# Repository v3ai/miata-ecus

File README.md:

# miata-ecus

A plug-in [rusEFI](https://rusefi.com) engine computer for the 1989–2005 Mazda Miata (NA and NB). It has two parts:

- **One universal daughterboard.** It does all the engine control: an STM32F407 running rusEFI, plus an on-board
  LSU 4.9 wideband controller (the open-source FOME/rusEFI design).
- **A motherboard for each model year.** Each one fits the stock ECU case, takes the stock harness connector and
  carries the year-specific wiring, the MAP sensor, the wideband sensor plug, the add-on header and USB-C.

The daughterboard plugs into the motherboard on two 1×40 sockets and four M3 standoffs.

<table>
<tr>
<td width="50%"></td>
<td width="50%"></td>
</tr>
<tr>
<td align="center"><sub>Daughterboard lifted off its sockets and standoffs</sub></td>
<td align="center"><sub>The universal daughterboard (rev 0.10)</sub></td>
</tr>
</table>

<sub>Renders from the 3D viewer in <a href="viewer/"><code>viewer/</code></a>, with black solder mask (<code>MASK=black</code> in <code>viewer/pcb3d.py</code>). The harness header, the wideband connector, the card socket, the MAP sensor and the heater fuse F1 are simplified stand-in models.</sub>

**Fitting one to a car:** [INSTALL.md](INSTALL.md) has labelled pictures of every connector, the header pin maps, the
MAP hose and wideband for each year, and the first start.

## Features and limitations

No board has been built yet. "Can" below means the hardware is designed for it and the firmware is set up for it; where
the firmware part has run in [emulation](firmware/sim/), that is as far as the proof goes.

### What it can do

**On every year**
- **Plugs into the stock harness** and fits the stock ECU's case (1990–95; the 1996–2005 fit is unchecked).
- **Fuel from manifold pressure** (speed-density), with the MAP sensor on the board. The stock airflow meter is not
  used and can come out of the intake.
- **MAP sensor good for boost:** 15–700 kPa absolute, so a turbo or supercharger needs no sensor change.
- **Wideband oxygen sensor controller on the board** for a Bosch LSU 4.9. No separate gauge or controller box. The
  board's connector takes AEM's ready-made X-Series sensor harness (30-3427).
- **Closed-loop fuel from the wideband**, switched on from the first start: ±10 % at idle and cruise, +10 / −5 %
  under load.
- **A base tune for each year**, loaded by the year button in TunerStudio ([what is in it](firmware/README.md#base-tune)).
- **Four injector outputs** for high-impedance injectors. Sequential on 1994–2005; in pairs on 1989–93, as the
  stock harness is wired (a jumper pair on that board is for a sequential conversion).
- **Four ignition outputs** (5 V logic): two on the harness for the stock coils, two more on the AUX header for one
  coil per cylinder.
- **Closed-loop idle** (on cars with a throttle position sensor), radiator fan, second fan, A/C clutch, fuel pump,
  check-engine light and tachometer, on the stock wires.
- **One USB-C port** for tuning (TunerStudio) and firmware updates, including the wideband's firmware.
- **Logging to a microSD card** in a socket on the daughterboard (rusEFI's own logger).
- **Protected outputs.** Every driver limits its current and shuts down when it overheats. In simulation every
  harness pin was shorted to ground, 14.4 V and 24 V; what still fails is listed in
  [VERIFICATION.md](VERIFICATION.md#rev-08-driver-temperature-and-protected-outputs).

**By year**

| | 1989–93 | 1994–95 | 1996–97 | 1999–2000 | 2001–05 |
|---|---|---|---|---|---|
| Injection | pairs | sequential | sequential | sequential | sequential |
| Variable valve timing | – | – | – | – | closed loop, rusEFI's target table |
| Knock sensor | add your own | add your own | add your own | stock sensor | stock sensor |
| Alternator voltage | alternator's own | alternator's own | alternator's own | ECU, ships off | ECU, ships off |
| Main relay held by the ECU | – | – | – | – | 2003–05 |
| Stock oxygen-sensor heater | – | – | driven | driven | not driven |
| Throttle position | switch only on manual cars | sensor | sensor | sensor | sensor |

**For a turbo and other add-ons** (the 20-pin add-on header, [pin map](INSTALL.md#header-pin-maps))
- Boost-control valve output, already assigned in the firmware, with a fused 12 V for the valve.
- **Flex-fuel sensor input** (GM / Continental type).
- **Nitrous arming input** for rusEFI's nitrous control.
- **CAN bus** for a dash or gauges: the bus the on-board wideband reports on.
- Knock sensor input for the cars that have none.
- Coil 3 and coil 4 outputs.
- A spare 0–5 V analog input, two inputs for magnetic (VR) crank and cam sensors, 5 V and a fused 12 V.
- rusEFI's own functions are all in the firmware (launch control, boost by table or closed loop, knock retard,
  general-purpose PWM tables, Lua scripts). None of them is set up or tested on this board.

### What it can't do

- **It is untested.** No board has been assembled, powered or run in a car.
- **The base tune is a starting point.** The tables came from other people's cars. Nobody has tuned them under
  boost, and the 1989–97 fuel table stops at 128 kPa.
- **No drive-by-wire throttle.** Every supported car has a cable throttle; this only matters for an engine swap.
- **High-impedance injectors only**, and the ignition outputs need coils with built-in igniters or the stock
  igniter. They can't drive a bare coil.
- **One wideband**, four cylinders.
- **The stock case has to be cut** for the wideband plug, USB-C, the MAP hose and the add-on ribbon cable. The
  1996–2005 boards still have the 1990–95 outline and mounting holes.
- **The add-on header is a ribbon-cable header inside the case**, not a sealed plug, and its 12 V pin is fused at
  1.1 A.
- **Sustained high rpm in a hot cabin is the thermal limit**, most of all on 1989–93 cars: see
  [Things to know before ordering](#things-to-know-before-ordering).
- **1990–93:** the fuel pump is switched by the airflow meter, so removing the meter needs one added wire
  ([INSTALL.md](INSTALL.md#199093)). Manual cars have no throttle position sensor until one is
  [fitted](#throttle-position-sensor-198993-manual-cars).
- **1999–2005:** alternator control ships switched off until the wire has been checked on a car.
- **Not street legal as an emissions device.** No OBD-II diagnostics or readiness monitors, no immobiliser, and it
  doesn't run the EGR valve, the 1999–2005 purge valve, the 2001–05 intake shutter valves (VTCS) or the rear oxygen
  sensor. The 1999–2000 VICS solenoid is wired but not set up.
- **Automatic cars are untested**, and the transmission unit's signals are mostly left unconnected.
- **2004–05 Mazdaspeed is not supported.**

> **Status:** every board is fully routed and passes KiCad DRC (no clearance errors, no unconnected items), and each
> schematic's netlist has been checked pad-by-pad against its board. **None of them has been built or tested yet**, and
> no person has reviewed the schematics. Read each board's README, especially its *Still to verify* or *Before ordering* list.
>
> **Verification (desk + simulation, 2026-10-30):** [VERIFICATION.md](VERIFICATION.md). Pinouts and firmware check out
> for all five years (after fixing a firmware bug that would have cut fuel and spark on 1996-2002 cars). The hardware
> changes it called for are in daughterboard rev 0.5 and motherboards rev 0.6 (1989-95) / 0.4 (1996-2005):
> - 5 V drive for the low-side drivers, held off until the firmware runs;
> - freewheel diodes on the idle and VVT valves;
> - BOOT1 pull-down;
> - no 2003-05 key-off back-feed;
> - a fused, clamped logic supply and a fused AUX +12 V pin;
> - clamped crank/cam inputs;
> - two drivers per injector wire on 1989-93.
>
> Every fix was re-simulated. Two wires still need checking on a car.
>
> **Full-firmware emulation (2026-11-02):** the unmodified rusEFI firmware runs on an emulated STM32F407 through every
> model year with 0 failures (two firmware bugs found and fixed). It flashes a blank emulated wideband STM32F103, which
> then reports lambda over CAN (`firmware/sim/`). The expanded circuit and fault checks found 13 new hardware items
> (N1-N13). Daughterboard rev 0.7 and the motherboards' 3 A heater fuse fixed most of them; see
> [Rev 0.7](VERIFICATION.md#rev-07-fixes-for-the-2026-11-02-findings).
>
> **Rev 0.8 (2026-11-03):** a larger daughterboard (125 × 76 mm) with DPAK injector drivers on drain copper and thermal
> vias (estimated 110 °C at 90 % duty and 85 °C ambient, where rev 0.7 reached thermal shutdown), protected relay, lamp,
> tach and ignition outputs, a separate protected 5 V for the harness sensors, LSU drive clamps, a +3V3 shunt clamp and
> fault-tolerant CAN transceivers. Every harness cavity shorted to ground, 14.4 V and 24 V: 4 failures left (rev 0.7:
> 215), all the LSU drive resistors taking a battery short so the ICs don't. See
> [Rev 0.8](VERIFICATION.md#rev-08-driver-temperature-and-protected-outputs).
>
> **Rev 0.9:** layout only. J1 is back on the daughterboard's top edge with the driver strip below it, and the
> daughterboard sits 16 mm lower, centred on each motherboard. Re-checked: same results as rev 0.8.
>
> **1989–93 motherboard rev 0.11:** the manual cars' throttle position sensor conversion uses the stock throttle switch
> plug, through three 0 Ω links. Pin 1N is no longer wired straight to the sensor 5 V, which the stock switch would have
> shorted at every idle. See [Throttle position sensor (1989–93 manual cars)](#throttle-position-sensor-198993-manual-cars).
>
> **Rev 0.10 (2026-11-13):** the daughterboard is now six layers in the same outline, with a turn-off clamp per
> injector, a microSD socket and flex-fuel and nitrous inputs; the motherboards take AEM's wideband harness and have a
> 20-pin add-on header with CAN, and 1989–93 and 1994–95 share one board set by jumpers. Before the layout every
> figure the design rests on was read again from its maker's document. That found a series resistor the injector
> drivers' inputs should always have had, and showed that the injector inductance behind every temperature estimate
> was a guess. A model of the whole board's copper now gives those temperatures. See
> [Rev 0.10](VERIFICATION.md#rev-010-six-layers-injector-clamps-card-socket-two-more-inputs-2026-11-13).
>
> **2026-11-14:** the motherboards' wideband connector was the wrong series (a guess); it is now the JST header
> that AEM's instructions point to (motherboards rev 0.13 / 0.9, routed again). The full-firmware emulation was run
> again with the rev 0.10 firmware, and the pictures and 3D viewer were redrawn from the current boards.
>
> **The boards ordered in November 2026** are the set before this (daughterboard rev 0.9). Their files are kept in
> [`ordered-boards/2026-11/`](ordered-boards/2026-11/); what the rev 0.10 review means for them is in
> [VERIFICATION.md](VERIFICATION.md#the-ordered-rev-09-boards).

| Board | Folder | Rev | Harness header | Case fit |
|---|---|---|---|---|
| Daughterboard (all years) | [`daughterboard/`](daughterboard/) | 0.10 | 2 × 1×40 to the motherboard | 125 × 76 mm, 6 layers |
| 1989–95 (NA6 and NA8; jumpers set 1989–93 or 1994–95) | [`motherboards/1989-95/`](motherboards/1989-95/) | 0.13 | TE 174917-6, 48 pins | stock NA case outline |
| 1996–97 (NA8, OBD-II) | [`motherboards/1996-97/`](motherboards/1996-97/) | 0.9 | TE 178780-1, 76 positions | **provisional** (NA outline) |
| 1999–2000 (NB1) | [`motherboards/1999-2000/`](motherboards/1999-2000/) | 0.9 | TE 178780-1, as 1996–97 (the car's own is the 64-position 176122-6; its plugs are the same housings) | **provisional** (NA outline) |
| 2001–05 (NB2, VVT) | [`motherboards/2001-05/`](motherboards/2001-05/) | 0.9 | TE 353830-5, 72 positions | **provisional** (NA outline) |

Each board folder contains:
- the KiCad 7 project (schematic and board);
- a schematic PDF;
- JLCPCB gerbers, BOM and placement files in `fab/`, with the DRC report, named for the board and revision (for example
  `miata-ecu-motherboard-1989-95-rev0.13_jlcpcb_gerbers.zip`). The JLC BOM is the SMD parts (and USB-C);
  `…_self_order_bom.csv` is everything you order and solder yourself, and
  [`additional-parts/order_all_boards.csv`](additional-parts/order_all_boards.csv) adds up every motherboard, a daughterboard for each and the in-car parts
  (the same list as a page with quantities and tick boxes: [`additional-parts/shopping_list.html`](additional-parts/shopping_list.html));
- renders;
- a README with the pinout, assembly notes and open questions.

## Firmware and flashing
The rusEFI board definition is in [`firmware/`](firmware/): pin map, year presets, and a flasher for the wideband MCU.
GitHub Actions builds it on every push: the firmware, the rusEFI console bundle and the TunerStudio `.ini`.
See [`firmware/README.md`](firmware/README.md). It compiles, but hasn't run on hardware yet.
- **One USB-C port for everything.** The USB-C on the motherboard's bottom edge goes to the main MCU (STM32F407).
  - **First flash:** ST's DFU mode (hold BOOT, tap RESET).
  - **Later updates:** from the rusEFI console through the OpenBLT bootloader, with no buttons to press.
  - **Tuning:** TunerStudio over the same port. Popular Vehicles picks the model year; the tune is stored in the
    MCU's flash.
- **The wideband MCU (STM32F103) is programmed through the main MCU.** With the engine off, press "Flash on-board
  wideband" in TunerStudio, or type `wbo_uart_flash` in the rusEFI console.
  - The main MCU controls the F103's BOOT0 and reset lines and writes the wideband firmware through the F103's
    built-in ST serial bootloader. The firmware is rusEFI's wideband controller with this board's port
    (`firmware/wideband`), and the main firmware carries it.
  - The SWD Tag-Connect pads on the bottom of the daughterboard (J102) are a fallback.

## Air temperature sensor
The stock sensor's harness wire goes straight to the ECU's air-temperature input: inside the airflow meter on 1989–97,
in the air filter box on 1999–2005. There is no separate connector for it on the board since motherboard rev 0.12 / 0.8.
With the airflow meter or airbox removed, put an open-element sensor on the stock sensor's plug
([INSTALL.md](INSTALL.md#7-air-temperature)) and pick its curve in TunerStudio. The firmware already accounts for the
board's 2.7 kΩ pull-up and divider.

## Throttle position sensor (1989–93 manual cars)
The 1989–93 manual cars have no throttle position sensor: the part on the throttle body is a switch with an idle
contact and a full-throttle contact. The automatics have a real 0–5 V sensor on 2M, as do all 1994–2005 cars. The ECU
calculates fuel from its MAP sensor, so a manual car runs without one, but rusEFI then treats the throttle sensor as
failed: no closed-loop idle, no throttle-based acceleration fuel and no overrun fuel cut.

The switch's plug has three wires: idle contact (1N), ground (2D) and full-throttle contact (2L). A sensor needs
three: 5 V, ground and signal. So, as on rusEFI's Hellen NA6 and MRE boards, a sensor plugs into the stock plug and the
1989–95 motherboard sets those pins with 0 Ω links: **fit R28** (5 V on 1N) and **move R29 to R30** (2L to
the throttle input). The kit, in the board's self-order BOM as "Manual cars":
- **Sensor:** a Kia sensor with the same 3-pin Mazda plug (Kia 0K01118911, or the others the
  [rusEFI wiki](https://wiki.rusefi.com/Legacy-Miata-NA-48-pin-board-for-MRE) lists).
- **Mount:** [Mazda NA6 Miata variable TPS mount](https://www.thingiverse.com/thing:3414132), printed in ASA.
- **Or instead:** [Flyin' Miata's TPS upgrade kit](https://flyinmiata.com/products/tps-upgrade) with its sensor.

Check the plug's wiring and the sensor's pins on your car before fitting R28: see the
[1989–95 README](motherboards/1989-95/README.md). Automatics leave R28 and R30 off.

## Things to know before ordering
- **Measure one injector's inductance first** (LCR meter, injector unplugged). The heat the injector clamps put into
  the board scales with it, and it is not known for Miata injectors: the design is sized for 20 mH, earlier revisions
  assumed 8 mH. At sustained 7200 rpm with 20 mH injectors the board model puts the processor 32–40 °C above the air
  around the board on 1994–2005 cars and 42–54 °C on 1989–93 cars, against a 105 °C junction rating. The 125 °C grade
  of the processor (STM32F407VGT7) fits the same pads and costs about five times as much. Numbers and options:
  [VERIFICATION.md](VERIFICATION.md#board-temperature).
- **The wideband connector has not been tried with a harness.** The motherboards carry a JST PUD header
  (S08B-PUDSS-1) for AEM's X-Series sensor harness 30-3427. AEM's instructions name the harness's terminal, and that
  terminal belongs to this connector series; AEM does not say which cavity is pin 1, so the board follows JST's
  numbering and prints each pin's wire colour beside the connector. Compare a harness with the print before the first
  use ([INSTALL.md](INSTALL.md#header-pin-maps)).
- **Clamp TVS stock.** The daughterboard's injector clamp TVS (Vishay TPSMC16A) is in JLCPCB's library, but its stock
  could not be confirmed; the [daughterboard README](daughterboard/README.md#before-ordering) names the alternate.
- **1996–2005 case geometry is a placeholder.** These motherboards use the NA board outline and mounting holes until a
  stock 96–97 / NB case is measured. The 76-pin 96–97 header is 130 mm wide and must clear the real case.
- **2001–05 Mazdaspeed:** pin 4R is the second intake-air-temperature sensor on the turbo cars, not the VVT valve.
  Don't fit the 01–05 board to a Mazdaspeed unmodified.
- **Wideband layout is new.** The wideband *circuit* is FOME's proven design. Since daughterboard rev 0.3 its *layout*
  is this board's own, so bring it up and check it against a known sensor before relying on it.
- **MAP sensor:** an MPX5700AP (absolute, single barb), fitted flat with its marking up. The barb's position on the
  footprint was taken from a photo; check it against a real part.

## Repository layout
| Path | What |
|---|---|
| `daughterboard/`, `motherboards/<years>/` | The released boards (see above) |
| `scripts/` | The design source. Every board is generated from Python: parts, netlist, placement, a grid router, schematic generation, release packaging |
| `mb/ecu_mb.pretty/` | Project footprints (harness headers named by OEM terminal, the flat MPX5700AP, USB-C, M4 case hole) |
| `research/` | Pinout research for 1996–2005 (sources compared per pin); the rev 0.10 design audit (every figure the board relies on, its source, and what could not be checked); ST's pin data files |
| `ordered-boards/2026-11/` | The board set ordered in November 2026 (daughterboard rev 0.9), as ordered |
| `viewer/` | Interactive 3D viewer: the daughterboard alone, or assembled on any year's motherboard. Click a part for its details and shop links |
| `firmware/` | The rusEFI board definition, the wideband flasher, the simulation tests and the verification tools. rusEFI itself is a submodule in `firmware/ext/rusefi` |
| `website/` | A black-and-white Shopify theme for selling the boards, draft product listings and product photos ([website/README.md](website/README.md)) |
| `INSTALL.md` | Fitting the ECU to a car: labelled pictures, header pin maps, the MAP hose and wideband per year, first start |
| `images/` | Renders, and the labelled pictures and pin maps (`scripts/annotate.py` redraws those from the board files) |
| `VERIFICATION.md` | Pinout, datasheet, simulation, flashing and safety review, with the hardware changes it calls for |
| `.github/workflows/firmware.yaml` | CI: checks the pin map against the board design and builds the firmware |

## Rebuilding
You need:
- **KiCad 7.0** with its Python `pcbnew` module, and `kicad-cli`;
- **Python 3** with `shapely` 2, `numpy`, `scipy`, `Pillow`, `openpyxl` and `matplotlib`;
- **`rsvg-convert`**, for the renders.

```sh
# daughterboard: build, route, finish, then the release folder
LAYERS=6 scripts/daughter_make.sh work/daughter
scripts/daughter_release.sh work/daughter/finished.kicad_pcb out/daughterboard

# a motherboard: <year module> <short name> <rev>, e.g. 1999-2000
scripts/mb_make.sh mb_nb1 9900 0.9      # writes mb/release_9900
```

Routing takes 10–40 minutes per motherboard and about an hour for the daughterboard.

`mk_hdr_fp.py` reads the harness-header geometry from the rusEFI hellen-one boards and KiCad library. Point it at them
with `MIATA_REF` and `RUSEFI_LIBS`. The generated footprints are already in `mb/ecu_mb.pretty/`.

The firmware build is described in [`firmware/README.md`](firmware/README.md).

The viewer is a static page. To open it, run `cd viewer && python3 -m http.server`, then browse to `http://localhost:8000`.
`viewer/pcb3d.py` rebuilds its assets from a board; it also needs `trimesh`, `cascadio`, `Pillow` and `gltfpack`.

The labelled pictures and pin maps in [INSTALL.md](INSTALL.md) come from the viewer and the board files:
`scripts/annotate.py --three <unpacked three@0.160.0 package>` redraws them (needs Playwright with Chromium, and `Pillow`).
`scripts/render_photos.py` renders the pictures at the top of this page and the shop's product photos the same way,
from a black-mask build of the viewer's assets.

## Credits and licences
- This project (the board designs, scripts and viewer) is released under the [MIT licence](LICENSE).
- One firmware file is GPL-3.0: `firmware/board/miata_nb_tune.cpp` holds the 1999–2005 base tune tables, copied from
  rusEFI. The firmware you build includes rusEFI, so the built firmware is GPL-3.0 as a whole
  ([firmware/README.md](firmware/README.md#licences)).
- The wideband controller circuit is the FOME / rusEFI open-source wideband module
  ([mck1117/wideband](https://github.com/mck1117/wideband), `board_module` rev C, MIT licence). Its source files and
  licence are in `scripts/wideband_ref/`.
- The circuit topologies follow rusEFI's hellen-one modules, and the harness pinouts were cross-checked against the
  rusEFI hellen Miata boards and the Mazda workshop manuals (see `research/`).

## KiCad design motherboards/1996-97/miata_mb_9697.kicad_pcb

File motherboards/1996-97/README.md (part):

# Miata ECU motherboard 1996-1997 (NA8 OBD2), rev 0.9

The motherboard replaces the stock Mazda ECU board inside the **stock ECU case**. It carries:

- the stock harness header;
- the year-independent I/O: the wideband sensor connector (AEM X-Series harness), USB-C, the MAP sensor and the add-on header (flex fuel, nitrous, CAN, boost);
- the sockets for the universal daughterboard, which does all the engine control (including the wideband controller).

## Changes in this revision
- Rev 0.9: the wideband sensor connector J2 is now a JST PUD side-entry header (S08B-PUDSS-1, two rows of four at 2.0 mm) instead of rev 0.8's Molex Micro-Fit 2x4. AEM's instructions for the X-Series gauge name the harness's replacement terminal, JST SPUD-001T-P0.5, which is the contact of JST's PUD series (plug housing PUDP-08V-S): a Micro-Fit header would not have taken the plug. The wire colour of each pin is printed beside the connector, to check a harness against by eye. The board is routed again; nothing else changed.
- Rev 0.8, for daughterboard rev 0.10 (a rev 0.9 daughterboard fits too, without the new functions). The wideband sensor connector J2 is a Molex Micro-Fit 2x4 for the off-the-shelf AEM X-Series sensor harness (30-3427) instead of the 2x3 for a hand-made lead; that plug family was a guess, and wrong: corrected in rev 0.9. The separate air-temperature connector J3 and its jumper are gone: the stock sensor's harness wire goes straight to the air-temperature input. The add-on header J5 is a 2x10 box header for a ribbon cable and gains the flex-fuel input (4.7k pull-up to 5 V, R35), the nitrous arming input (10k pull-down, R36) and the CAN bus; a boost valve on it has its own freewheel diode (D5), and its +12 V fuse F4 holds 1.1 A instead of 0.5 A. Harness header TE 178780-1 as before.
- Rev 0.7, for daughterboard rev 0.9: the daughterboard sits 16 mm lower, centred on the board (42 mm from the top, as up to rev 0.7), with its J1 on its top edge again: JD1 and the upper standoffs HD1/HD2 are back at their rev 0.7 places, JD2, the lower standoffs HD3/HD4, the AUX header J5 (with F4 beside it) and the parts placed against JD2 (CAN termination R1/R6, pull-up options) are 16 mm lower, and the board is routed again. Not compatible with a rev 0.8 daughterboard.
- Rev 0.6, for daughterboard rev 0.8: the harness's sensor 5 V (3I) and the AUX header pin J5-14 now come from the daughterboard's protected 5 V (V5_EXT, JD1 pin 13, which was a ground pin): a sensor 5 V wire shorted to the battery no longer back-feeds the MAP sensor and the ECU's own 5 V. The MAP sensor keeps its own supply (V5_SENS). The daughterboard outline on the silkscreen is 16 mm taller (125 x 76 mm): its new strip of output drivers overhangs the free area above JD1.
- Rev 0.5: LSU heater fuse F1 is a 3 A hold PTC (LUTE 2920L300/30GR, 30 V, 2920 size) instead of the 2 A 1812 part. A cold LSU 4.9 heater draws 1.6-2.3 A rms at the start of the wideband's warm-up, more than the old fuse holds once warm, so it could trip and the controller time out. No 1812 PTC holds 3 A above 8 V.
- Rev 0.4: freewheel diode D1 on the idle valve to its +12 V feed (the PWM turn-off energy no longer goes into the daughterboard driver); F4 resettable fuse on the AUX +12 V pin J5-15; not-fitted 12 V pull-up options R20-R22 for the VSS / A/C / clutch inputs.
- Rev 0.3: IAT source is now a removable jumper (JP1, 1x3 2.54 mm header + shunt) instead of the R4 / R5 0R links: shunt on EXT (default) reads the IAT connector J3, on STOCK the stock harness sensor; labelled on the silkscreen.
- Rev 0.2: MAP sensor is now the MPX5700AP (absolute, case 867B, one barb; LCSC C90152) instead of the MPX5700DP: new footprint with the real lozenge body and offset barb, holes on the NXP 23.11 mm spacing with 3.3 mm M3 clearance drills.
- Rev 0.1: first release (design complete, case geometry provisional).

## Files
| Path | What |
|---|---|
| `miata_mb_9697.kicad_pro / .kicad_sch / .kicad_pcb` | KiCad 7 project. Root schematic plus three sheets: harness, daughterboard, I/O |
| `miata_mb_9697_schematic.pdf` | Schematic PDF |
| `fab/miata-ecu-motherboard-1996-97-rev0.9_jlcpcb_gerbers.zip`, `fab/miata-ecu-motherboard-1996-97-rev0.9_jlcpcb_bom.csv`, `fab/miata-ecu-motherboard-1996-97-rev0.9_jlcpcb_cpl.csv` | JLC fabrication and assembly files (2 layers, 1.6 mm). The JLC BOM is the SMD parts and USB-C only |
| `fab/miata-ecu-motherboard-1996-97-rev0.9_self_order_bom.csv` | Everything you order and fit yourself: harness header, through-hole connectors, MAP sensor, shunt, standoffs and screws, plus the not-fitted options. Its columns load into LCSC's BOM tool |
| `fab/miata-ecu-motherboard-1996-97-rev0.9_parts_list.csv` | Every part, including the hand-fitted and not-fitted ones |
| `fab/drc_report.txt` | KiCad DRC |
| `ecu_mb.pretty/`, `fp-lib-table` | Project footprints (harness header, MAP sensor lying flat, USB-C, M4 case hole) |
| `renders/` | Top and bottom copper |
| `scripts/` | The design source; `mb_make.sh` rebuilds the whole board |

## Case fit
**PROVISIONAL.** No source gives this case's board outline and mounting holes yet (the open-source boards for these years either use their own enclosure or a different Mazda case). Until a stock board or case is measured, this board uses the NA case outline and holes as a stand-in, with the header centred on the top edge. Moving to the real outline is a change of OUTLINE / CASE_HOLES / HDR_1A in the year module plus an automatic reroute. **Do not order this board before the case is measured.**

Board: **154.0 × 161.5 mm**, 1.6 mm. The origin is the top-left corner and y points down, toward the bottom edge.

| Hole | x, y (mm) |
|---|---|
| H3 | 4.0, 84.0 |
| H4 | 150.0, 84.0 |
| H5 | 4.0, 143.0 |
| H6 | 150.0, 143.0 |

All holes are 4.5 mm plated with a 7 mm pad, tied to GND, for M4 screws. Harness header terminal 1A sits at (16.00, 18.13) mm (lower pin row).

## Harness header
TE **178780-1**, 76 positions (alternates 174915-6, 3-178780-6): OEM plug 1 = 1A-1V (22), plug 2 = 2A-2L (12, no harness plug: left open), plug 3 = 3A-3P (16), plug 4 = 4A-4Z (26). Hellen's board names the same cavities 1 / 4 / 2 / 3. Fitted by hand.

| Pin | Net | Use | Stock function / note |
|---|---|---|---|
| 1A | `OUT_FAN` | fan relay | cooling (radiator) fan relay |
| 1B | `OUT_LS7` | spare low side | fan No.2 / A/C condenser fan relay |
| 1E | `OUT_CEL` | check engine lamp | MIL |
| 1G | `OUT_AC` | A/C relay | A/C relay |
| 1K | `IN_SW2` | 12 V switch input 2 | A/C switch / refrigerant pressure switch |
| 1L | `IN_SW3` | 12 V switch input 3 | clutch switch |
| 1M | `IN_SW1` | 12 V switch input 1 | vehicle speed sensor |
| 1O | `GND` | ground | ground |
| 1U | `OUT_FP` | fuel pump relay | fuel pump relay |
| 3B | `IN_AUX3` | spare analog 3 | MAF signal |
| 3C | `IN_AUX2` | spare analog 2 | front HO2S (narrowband) |
| 3D | `IN_AUX1` | spare analog 1 | rear HO2S |
| 3F | `IN_TPS` | TPS | throttle position sensor |
| 3G | `IN_CLT` | coolant temp | coolant temperature sensor |
| 3I | `V5_EXT` | sensor 5 V reference (out; protected, short-to-battery proof) | +5 V sensor reference (TPS, MAF) |
| 3K | `IN_IAT` | air temperature (stock sensor) | intake air temperature sensor (in the airflow meter) |
| 3M | `OUT_VVT` | PWM low side (VVT driver) | front HO2S heater (PWM low side; no VVT on this engine) |
| 3O | `GND` | ground | sensor ground (BLK/BLU) |
| 4A | `GND` | ground | ground |
| 4B | `VBAT_IN` | ECU power (main relay) | ECU +12 V from the main relay (WHT/RED) |
| 4C | `GND` | ground |  |
| 4D | `GND` | ground |  |
| 4F | `IN_HALL1` | hall input 1 (crank) | CAS 4-pulse crank angle (SGT), hall / open collector |
| 4G | `IN_HALL2` | hall input 2 (cam) | CAS 2-pulse cam (SGC), hall / open collector |
| 4L | `OUT_TACH` | tach out | tachometer |
| 4N | `OUT_IGN1` | ignition 1 (5 V logic) | igniter cylinders 1 & 4 |
| 4Q | `OUT_IACV` | idle air valve | idle air control valve (low side) |
| 4R | `OUT_IGN2` | ignition 2 (5 V logic) | igniter cylinders 2 & 3 |
| 4U | `OUT_INJ1` | injector 1 |  |
| 4V | `OUT_INJ2` | injector 2 |  |
| 4W | `OUT_INJ3` | injector 3 |  |
| 4X | `OUT_INJ4` | injector 4 |  |

Not connected: 1C, 1D, 1F, 1H, 1I, 1J, 1N, 1P, 1Q, 1R, 1S, 1T, 1V, 2A, 2B, 2C, 2D, 2E, 2F, 2G, 2H, 2I, 2J, 2K, 2L, 3A, 3E, 3H, 3J, 3L, 3N, 3P, 4E, 4H, 4I, 4J, 4K, 4M, 4O, 4P, 4S, 4T, 4Y, 4Z.

## Bottom edge, left to right
| Ref | What | Notes |
|---|---|---|
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
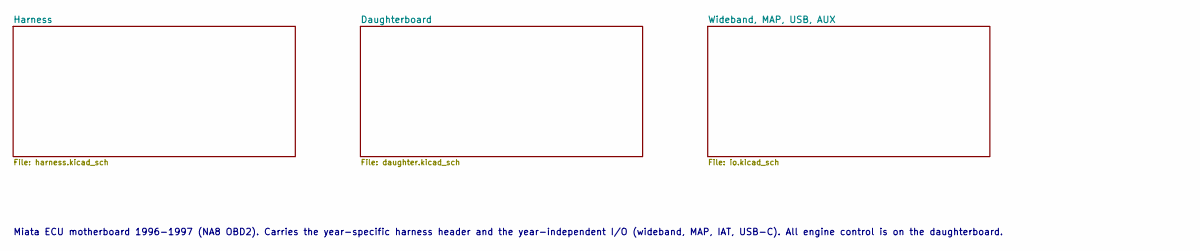
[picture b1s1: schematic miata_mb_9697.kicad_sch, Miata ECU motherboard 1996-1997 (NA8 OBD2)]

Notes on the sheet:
Miata ECU motherboard 1996-1997 (NA8 OBD2). Carries the year-specific harness header and the year-independent I/O (wideband, MAP, IAT, USB-C). All engine control is on the daughterboard.

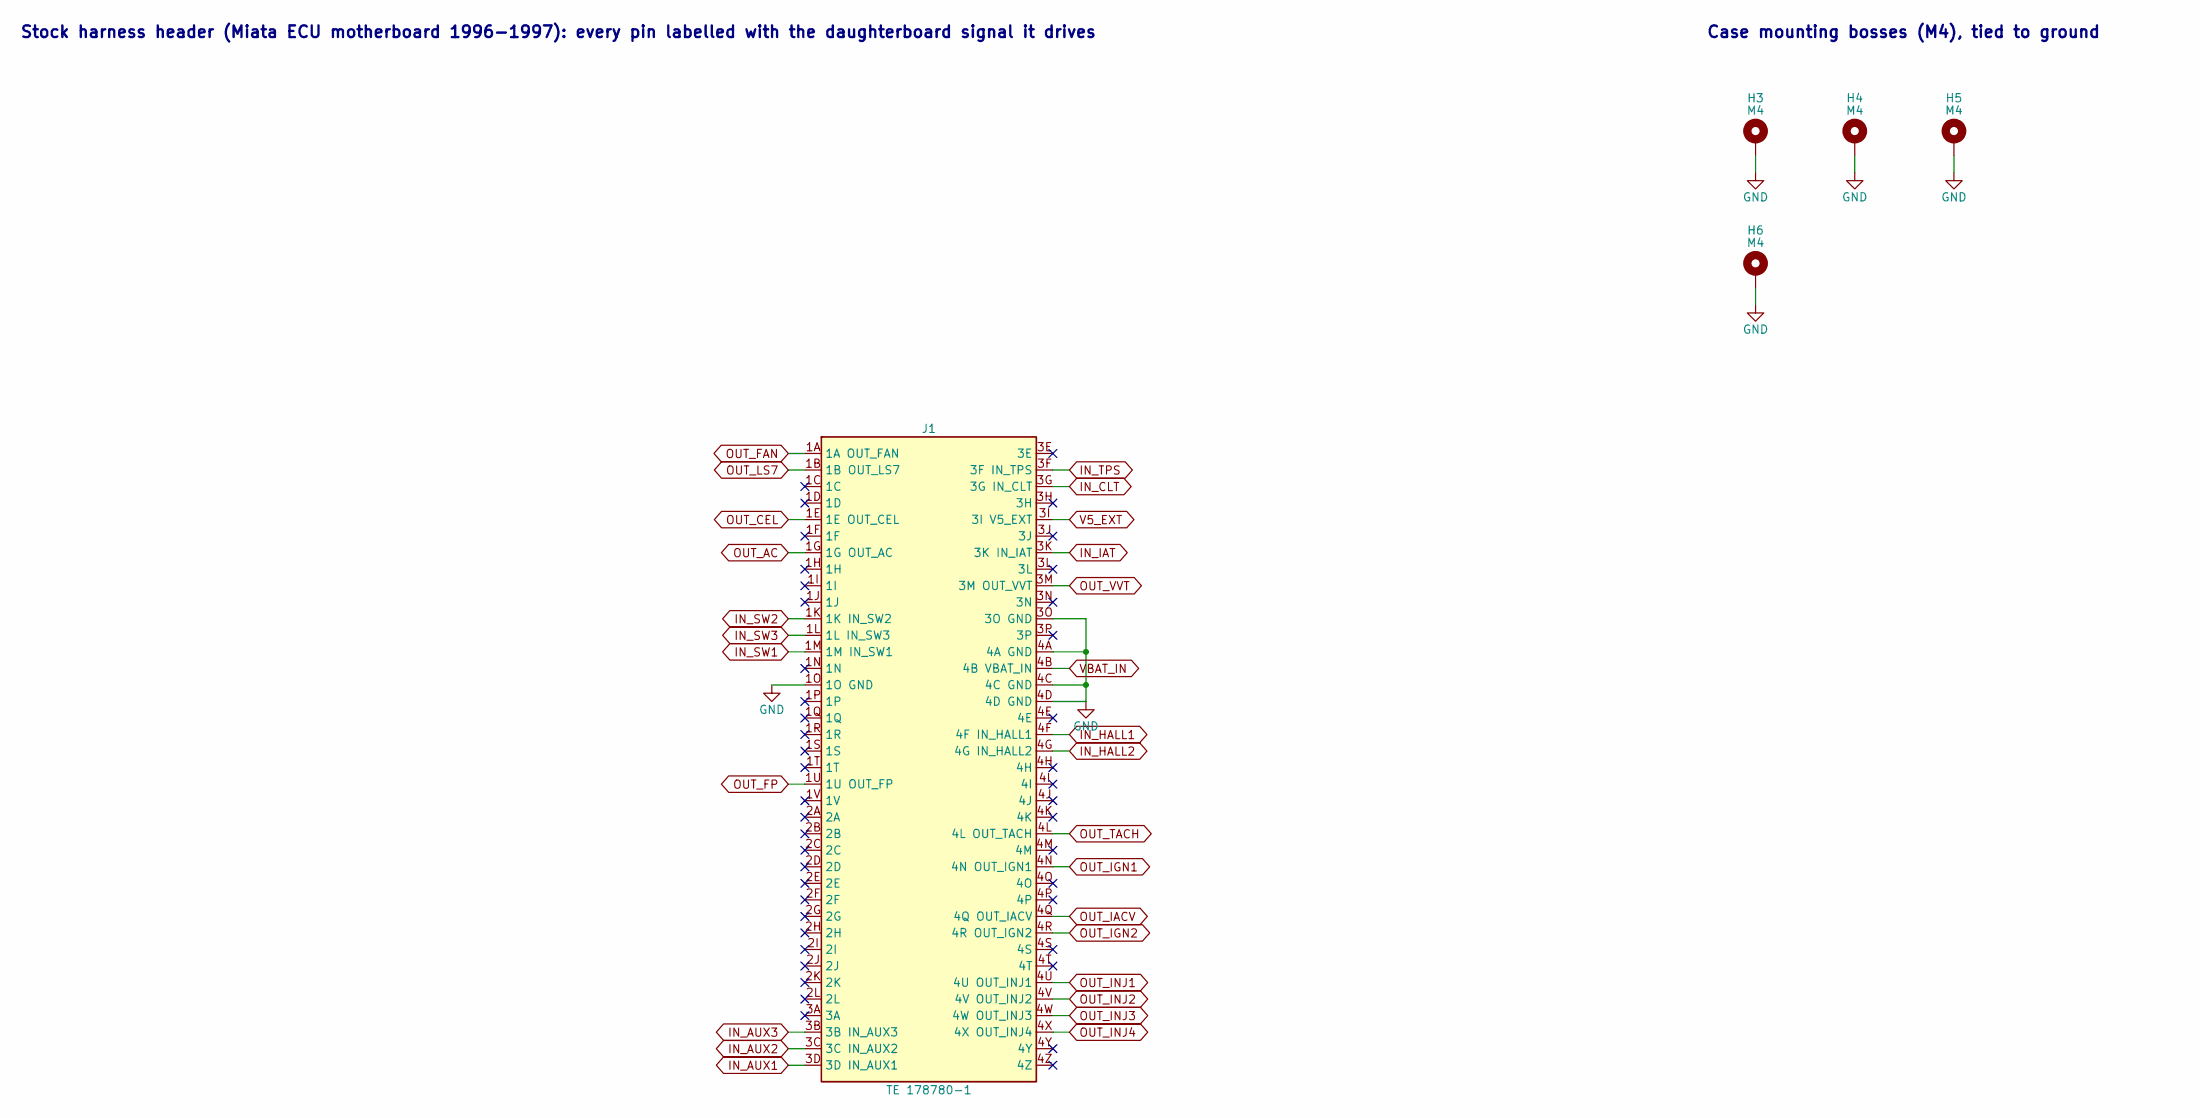
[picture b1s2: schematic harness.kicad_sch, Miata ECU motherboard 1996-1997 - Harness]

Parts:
H3, H4, H5, H6: M4; MountingHole_M4_4.5mm_Pad7
J1: TE 178780-1; TE_178780-1_76P

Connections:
GND: H3.1, H4.1, H5.1, H6.1, J1.1O (1O GND), J1.3O (3O GND), J1.4A (4A GND), J1.4C (4C GND), J1.4D (4D GND); also elsewhere on the board
IN_AUX1: J1.3D (3D IN_AUX1); also elsewhere on the board
IN_AUX2: J1.3C (3C IN_AUX2); also elsewhere on the board
IN_AUX3: J1.3B (3B IN_AUX3); also elsewhere on the board
IN_CLT: J1.3G (3G IN_CLT); also elsewhere on the board
IN_HALL1: J1.4F (4F IN_HALL1); also elsewhere on the board
IN_HALL2: J1.4G (4G IN_HALL2); also elsewhere on the board
IN_IAT: J1.3K (3K IN_IAT); also elsewhere on the board
IN_SW1: J1.1M (1M IN_SW1); also elsewhere on the board
IN_SW2: J1.1K (1K IN_SW2); also elsewhere on the board
IN_SW3: J1.1L (1L IN_SW3); also elsewhere on the board
IN_TPS: J1.3F (3F IN_TPS); also elsewhere on the board
OUT_AC: J1.1G (1G OUT_AC); also elsewhere on the board
OUT_CEL: J1.1E (1E OUT_CEL); also elsewhere on the board
OUT_FAN: J1.1A (1A OUT_FAN); also elsewhere on the board
OUT_FP: J1.1U (1U OUT_FP); also elsewhere on the board
OUT_IACV: J1.4Q (4Q OUT_IACV); also elsewhere on the board
OUT_IGN1: J1.4N (4N OUT_IGN1); also elsewhere on the board
OUT_IGN2: J1.4R (4R OUT_IGN2); also elsewhere on the board
OUT_INJ1: J1.4U (4U OUT_INJ1); also elsewhere on the board
OUT_INJ2: J1.4V (4V OUT_INJ2); also elsewhere on the board
OUT_INJ3: J1.4W (4W OUT_INJ3); also elsewhere on the board
OUT_INJ4: J1.4X (4X OUT_INJ4); also elsewhere on the board
OUT_LS7: J1.1B (1B OUT_LS7); also elsewhere on the board
OUT_TACH: J1.4L (4L OUT_TACH); also elsewhere on the board
OUT_VVT: J1.3M (3M OUT_VVT); also elsewhere on the board
V5_EXT: J1.3I (3I V5_EXT); also elsewhere on the board
VBAT_IN: J1.4B (4B VBAT_IN); also elsewhere on the board

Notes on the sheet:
Stock harness header (Miata ECU motherboard 1996-1997): every pin labelled with the daughterboard signal it drives
Case mounting bosses (M4), tied to ground

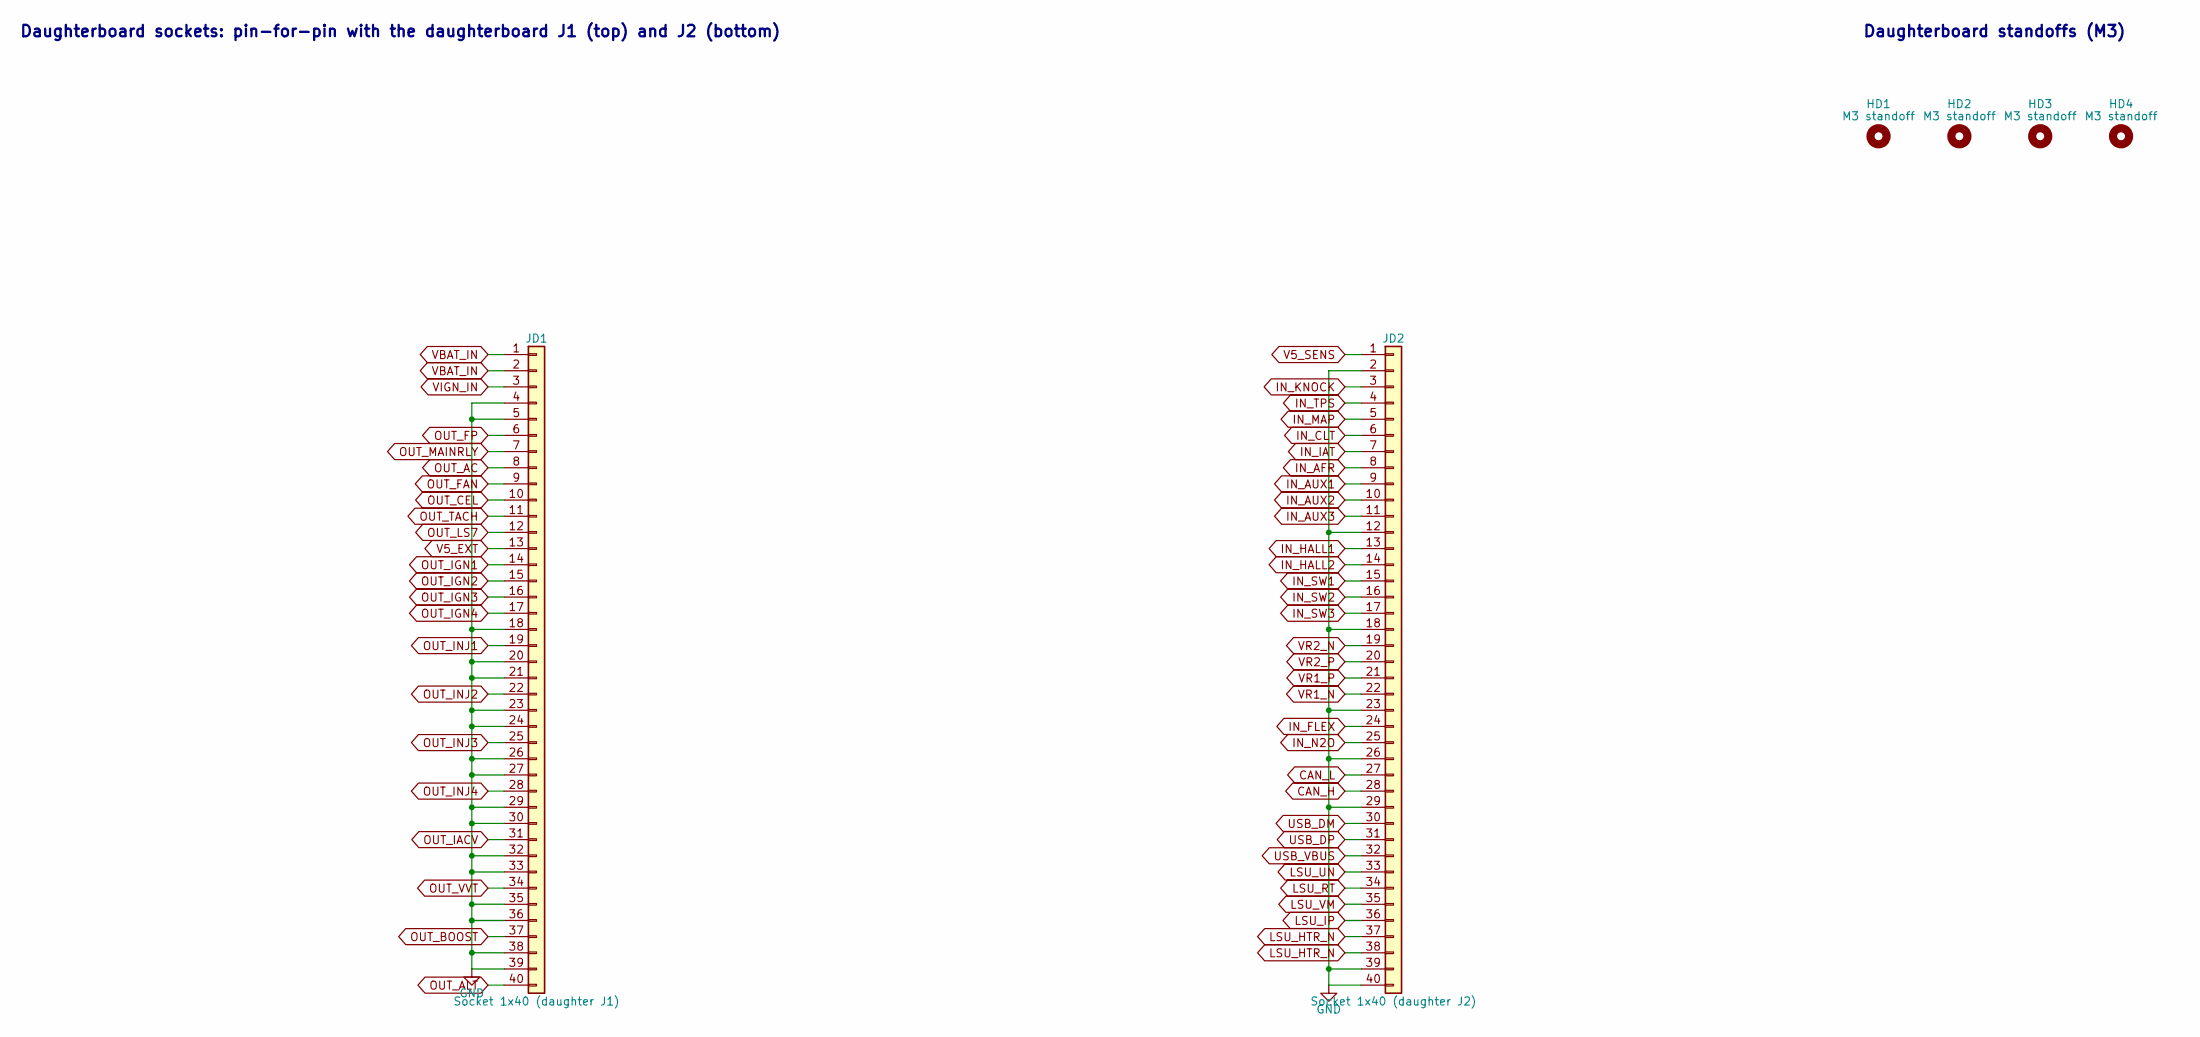
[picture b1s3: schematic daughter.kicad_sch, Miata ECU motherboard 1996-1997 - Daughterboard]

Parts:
HD1, HD2, HD3, HD4: M3 standoff; MountingHole_3.2mm_M3
JD1: Socket 1x40 (daughter J1); PinSocket_1x40_P2.54mm_Vertical; LCSC C124412
JD2: Socket 1x40 (daughter J2); PinSocket_1x40_P2.54mm_Vertical; LCSC C124412

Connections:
CAN_H: JD2.28; also elsewhere on the board
CAN_L: JD2.27; also elsewhere on the board
GND: JD1.4, JD1.5, JD1.18, JD1.20, JD1.21, JD1.23, JD1.24, JD1.26, JD1.27, JD1.29, JD1.30, JD1.32, JD1.33, JD1.35, JD1.36, JD1.38, JD1.39, JD2.2, JD2.12, JD2.18, JD2.23, JD2.26, JD2.29, JD2.39, JD2.40; also elsewhere on the board
IN_AFR: JD2.8; also elsewhere on the board
IN_AUX1: JD2.9; also elsewhere on the board
IN_AUX2: JD2.10; also elsewhere on the board
IN_AUX3: JD2.11; also elsewhere on the board
IN_CLT: JD2.6; also elsewhere on the board
IN_FLEX: JD2.24; also elsewhere on the board
IN_HALL1: JD2.13; also elsewhere on the board
IN_HALL2: JD2.14; also elsewhere on the board
IN_IAT: JD2.7; also elsewhere on the board
IN_KNOCK: JD2.3; also elsewhere on the board
IN_MAP: JD2.5; also elsewhere on the board
IN_N2O: JD2.25; also elsewhere on the board
IN_SW1: JD2.15; also elsewhere on the board
IN_SW2: JD2.16; also elsewhere on the board
IN_SW3: JD2.17; also elsewhere on the board
IN_TPS: JD2.4; also elsewhere on the board
LSU_HTR_N: JD2.37, JD2.38; also elsewhere on the board
LSU_IP: JD2.36; also elsewhere on the board
LSU_RT: JD2.34; also elsewhere on the board
LSU_UN: JD2.33; also elsewhere on the board
LSU_VM: JD2.35; also elsewhere on the board
OUT_AC: JD1.8; also elsewhere on the board
OUT_ALT: JD1.40; also elsewhere on the board
OUT_BOOST: JD1.37; also elsewhere on the board
OUT_CEL: JD1.10; also elsewhere on the board
OUT_FAN: JD1.9; also elsewhere on the board
OUT_FP: JD1.6; also elsewhere on the board
OUT_IACV: JD1.31; also elsewhere on the board
OUT_IGN1: JD1.14; also elsewhere on the board
OUT_IGN2: JD1.15; also elsewhere on the board
OUT_IGN3: JD1.16; also elsewhere on the board
OUT_IGN4: JD1.17; also elsewhere on the board
OUT_INJ1: JD1.19; also elsewhere on the board
OUT_INJ2: JD1.22; also elsewhere on the board
OUT_INJ3: JD1.25; also elsewhere on the board
OUT_INJ4: JD1.28; also elsewhere on the board
OUT_LS7: JD1.12; also elsewhere on the board
OUT_MAINRLY: JD1.7; also elsewhere on the board
OUT_TACH: JD1.11; also elsewhere on the board
OUT_VVT: JD1.34; also elsewhere on the board
USB_DM: JD2.30; also elsewhere on the board
USB_DP: JD2.31; also elsewhere on the board
USB_VBUS: JD2.32; also elsewhere on the board
V5_EXT: JD1.13; also elsewhere on the board
V5_SENS: JD2.1; also elsewhere on the board
VBAT_IN: JD1.1, JD1.2; also elsewhere on the board
VIGN_IN: JD1.3
VR1_N: JD2.22; also elsewhere on the board
VR1_P: JD2.21; also elsewhere on the board
VR2_N: JD2.19; also elsewhere on the board
VR2_P: JD2.20; also elsewhere on the board

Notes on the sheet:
Daughterboard sockets: pin-for-pin with the daughterboard J1 (top) and J2 (bottom)
Daughterboard standoffs (M3)

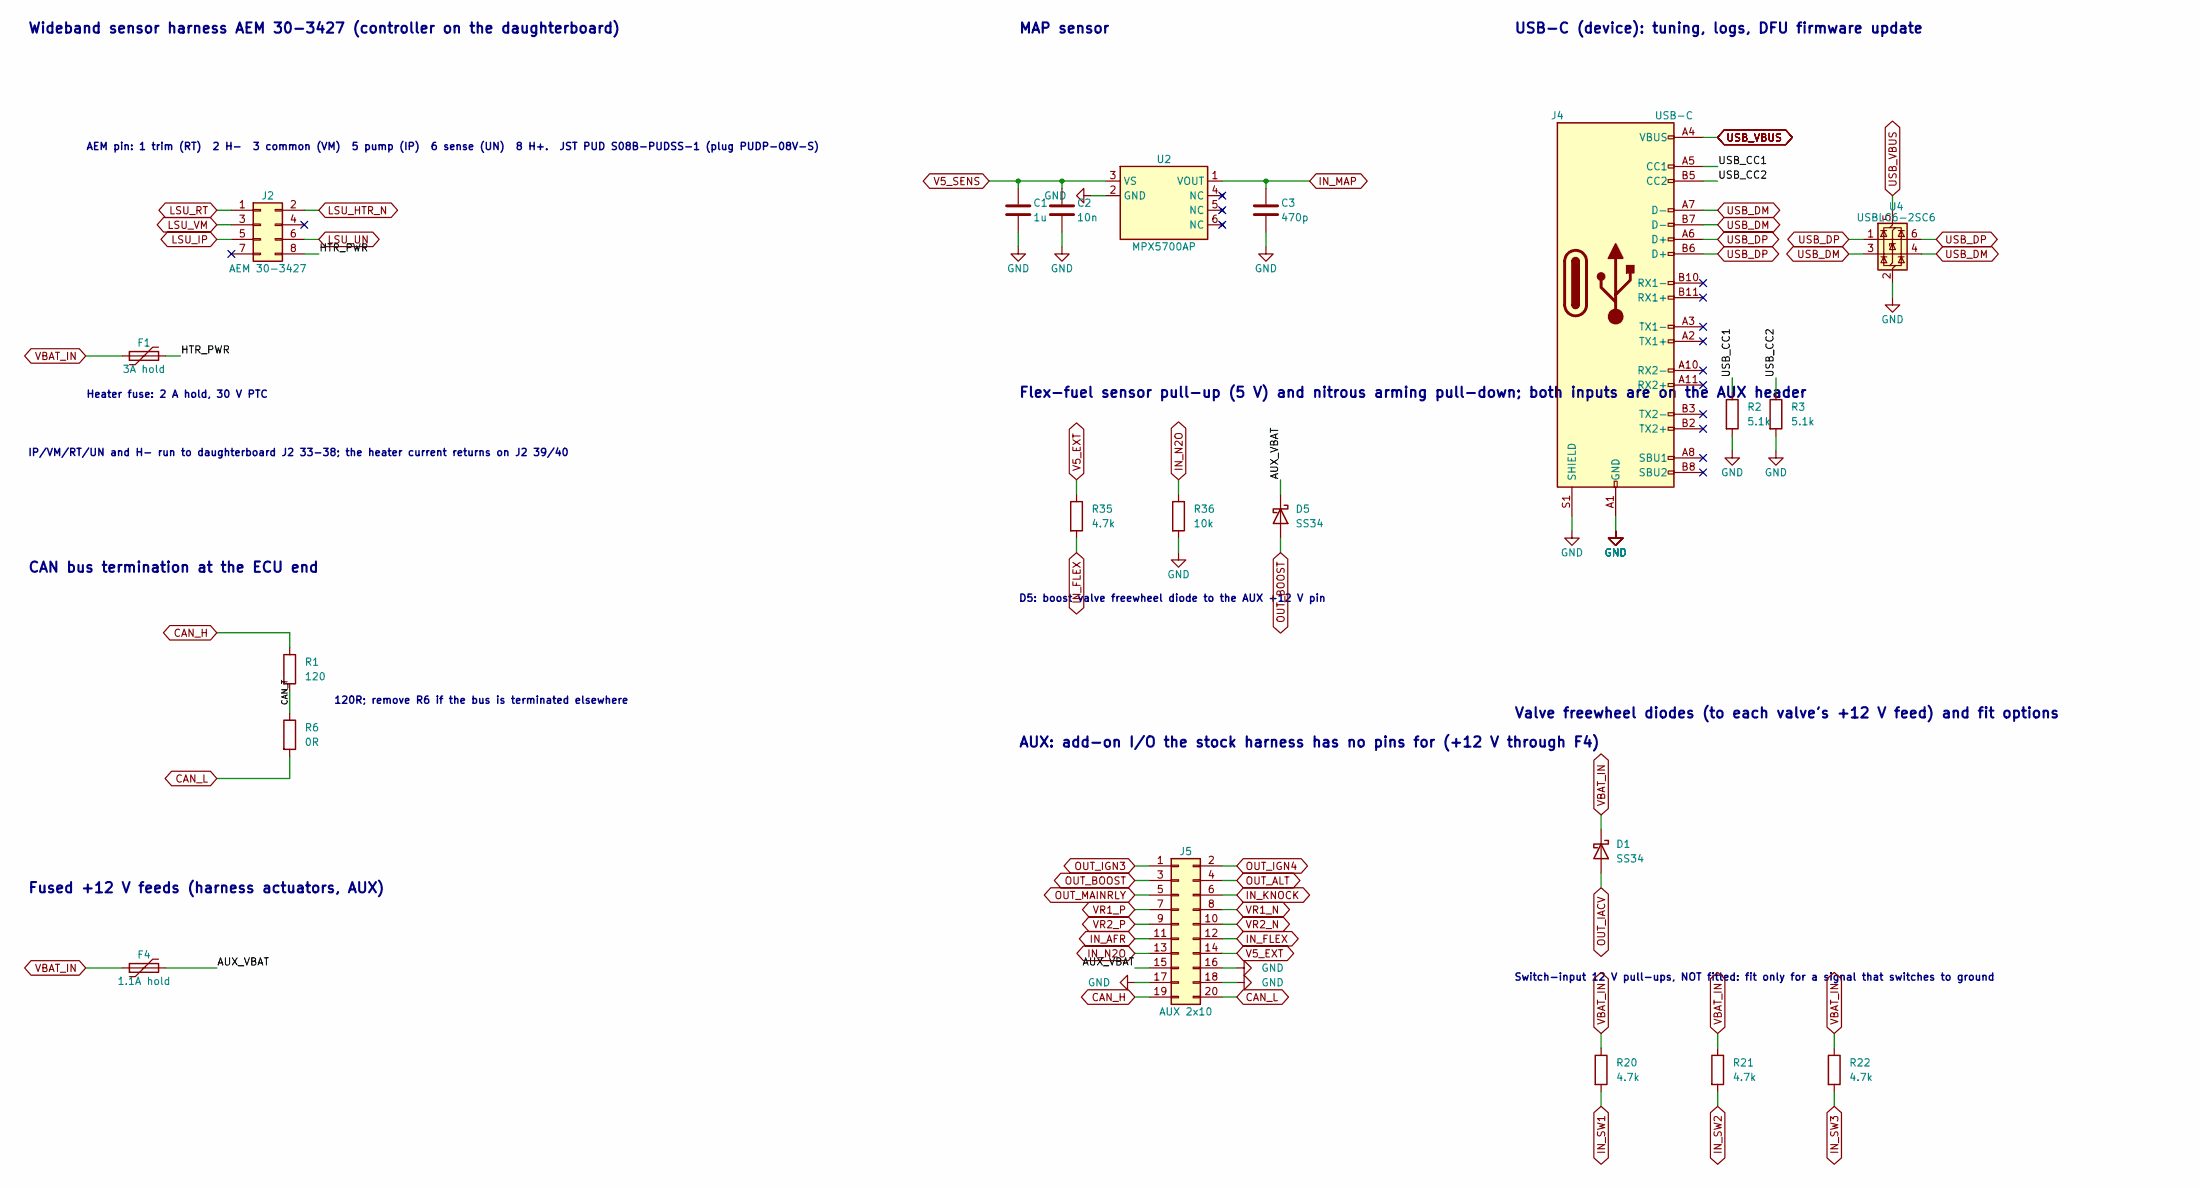
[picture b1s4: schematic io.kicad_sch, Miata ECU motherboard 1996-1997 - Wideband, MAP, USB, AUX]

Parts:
C1: 1u; C_0603_1608Metric; LCSC C15849
C2: 10n; C_0603_1608Metric; LCSC C57112
C3: 470p; C_0603_1608Metric; LCSC C1620
D1, D5: SS34; D_SMA; LCSC C8678
F1: 3A hold; Fuse_2920_7451Metric; LCSC C22446884
F4: 1.1A hold; Fuse_1812_4532Metric; LCSC C883150
J2: AEM 30-3427; JST_PUD_S08B-PUDSS-1_2x04_P2.00mm_Horizontal
J4: USB-C; USB_C_GCT_USB4105_16P; LCSC C3020560
J5: AUX 2x10; IDC-Header_2x10_P2.54mm_Vertical
R1: 120; R_0603_1608Metric; LCSC C22787
R2, R3: 5.1k; R_0603_1608Metric; LCSC C23186
R6: 0R; R_0603_1608Metric; LCSC C21189
R20, R21, R22: 4.7k; R_0603_1608Metric
R35: 4.7k; R_0603_1608Metric; LCSC C23162
R36: 10k; R_0603_1608Metric; LCSC C25804
U2: MPX5700AP; MPX5700AP_867B_Flat; LCSC C90152
U4: USBLC6-2SC6; SOT-23-6; LCSC C7519

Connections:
/Wideband, MAP, USB, AUX/AUX_VBAT: D5.1 (K), F4.2, J5.15
/Wideband, MAP, USB, AUX/CAN_T: R1.2, R6.1
/Wideband, MAP, USB, AUX/HTR_PWR: F1.2, J2.8
/Wideband, MAP, USB, AUX/USB_CC1: J4.A5 (CC1), R2.1
/Wideband, MAP, USB, AUX/USB_CC2: J4.B5 (CC2), R3.1
CAN_H: J5.19, R1.1; also elsewhere on the board
CAN_L: J5.20, R6.2; also elsewhere on the board
GND: C1.2, C2.2, C3.2, J4.A1 (GND), J4.A12 (GND), J4.B1 (GND), J4.B12 (GND), J4.S1 (SHIELD), J5.16, J5.17, J5.18, R2.2, R3.2, R36.2, U2.2 (GND), U4.2 (GND); also elsewhere on the board
IN_AFR: J5.11; also elsewhere on the board
IN_FLEX: J5.12, R35.2; also elsewhere on the board
IN_KNOCK: J5.6; also elsewhere on the board
IN_MAP: C3.1, U2.1 (VOUT); also elsewhere on the board
IN_N2O: J5.13, R36.1; also elsewhere on the board
IN_SW1: R20.2; also elsewhere on the board
IN_SW2: R21.2; also elsewhere on the board
IN_SW3: R22.2; also elsewhere on the board
LSU_HTR_N: J2.2; also elsewhere on the board
LSU_IP: J2.5; also elsewhere on the board
LSU_RT: J2.1; also elsewhere on the board
LSU_UN: J2.6; also elsewhere on the board
LSU_VM: J2.3; also elsewhere on the board
OUT_ALT: J5.4; also elsewhere on the board
OUT_BOOST: D5.2 (A), J5.3; also elsewhere on the board
OUT_IACV: D1.2 (A); also elsewhere on the board
OUT_IGN3: J5.1; also elsewhere on the board
OUT_IGN4: J5.2; also elsewhere on the board
OUT_MAINRLY: J5.5; also elsewhere on the board
USB_DM: J4.A7 (D-), J4.B7 (D-), U4.3 (I/O2), U4.4 (I/O2); also elsewhere on the board
USB_DP: J4.A6 (D+), J4.B6 (D+), U4.1 (I/O1), U4.6 (I/O1); also elsewhere on the board
USB_VBUS: J4.A4 (VBUS), J4.A9 (VBUS), J4.B4 (VBUS), J4.B9 (VBUS), U4.5 (VBUS); also elsewhere on the board
V5_EXT: J5.14, R35.1; also elsewhere on the board
V5_SENS: C1.1, C2.1, U2.3 (VS); also elsewhere on the board
VBAT_IN: D1.1 (K), F1.1, F4.1, R20.1, R21.1, R22.1; also elsewhere on the board
VR1_N: J5.8; also elsewhere on the board
VR1_P: J5.7; also elsewhere on the board
VR2_N: J5.10; also elsewhere on the board
VR2_P: J5.9; also elsewhere on the board

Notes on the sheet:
Wideband sensor harness AEM 30-3427 (controller on the daughterboard)
AEM pin: 1 trim (RT) 2 H- 3 common (VM) 5 pump (IP) 6 sense (UN) 8 H+. JST PUD S08B-PUDSS-1 (plug PUDP-08V-S)
IP/VM/RT/UN and H- run to daughterboard J2 33-38; the heater current returns on J2 39/40
Heater fuse: 2 A hold, 30 V PTC
CAN bus termination at the ECU end
120R; remove R6 if the bus is terminated elsewhere
MAP sensor
Flex-fuel sensor pull-up (5 V) and nitrous arming pull-down; both inputs are on the AUX header
D5: boost valve freewheel diode to the AUX +12 V pin
USB-C (device): tuning, logs, DFU firmware update
Fused +12 V feeds (harness actuators, AUX)
AUX: add-on I/O the stock harness has no pins for (+12 V through F4)
Valve freewheel diodes (to each valve's +12 V feed) and fit options
Switch-input 12 V pull-ups, NOT fitted: fit only for a signal that switches to ground

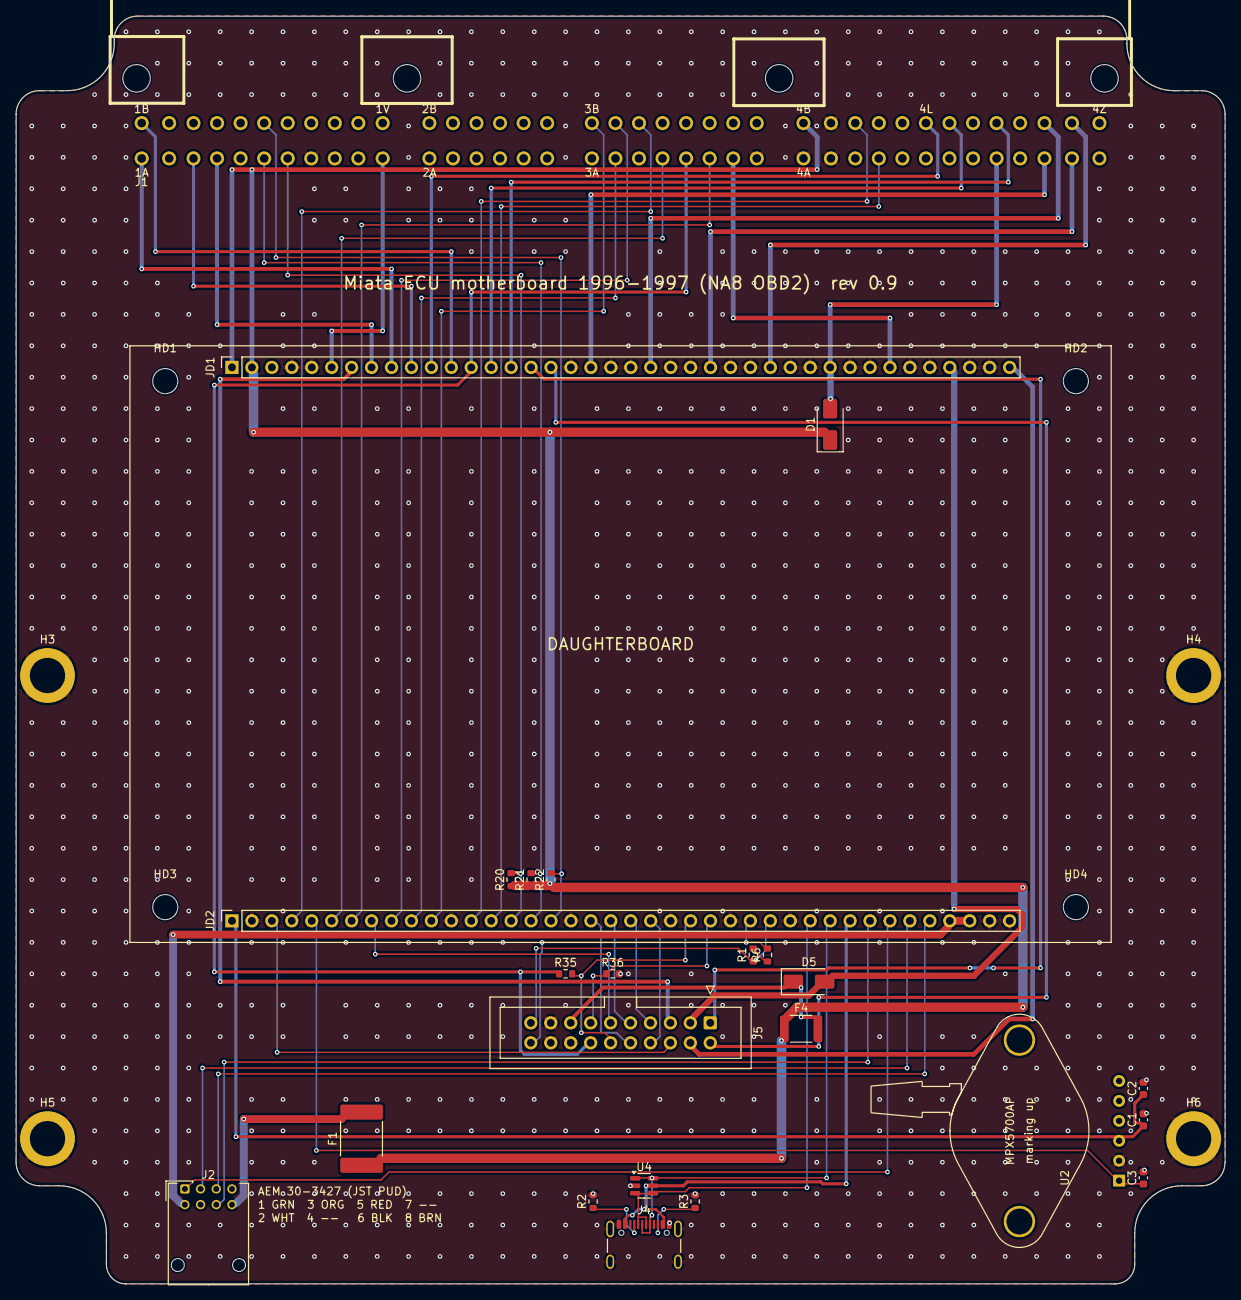
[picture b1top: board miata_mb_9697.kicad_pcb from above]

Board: 2 copper layers, 154.0 x 161.5 mm, 32 parts (0 on the bottom side), 58 nets.

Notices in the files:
daughterboard/README.md:
- **On-board wideband controller.** The complete FOME / rusEFI open-source wideband controller (MIT licence, github.com/mck1117/wideband, `board_module` rev C) is now on this board.
y` (parts + netlist), `placement.py`, `build_pcb.py`, `route.py`, `wideband.py` (the wideband circuit, mapped from the FOME module in `wideband_ref/` under its MIT licence), `wb_clean.py` (its rev 0.3 placement and heater copper; `wb_preview.py` draws a placement preview), `wb_build.py` (the rev 0.2
